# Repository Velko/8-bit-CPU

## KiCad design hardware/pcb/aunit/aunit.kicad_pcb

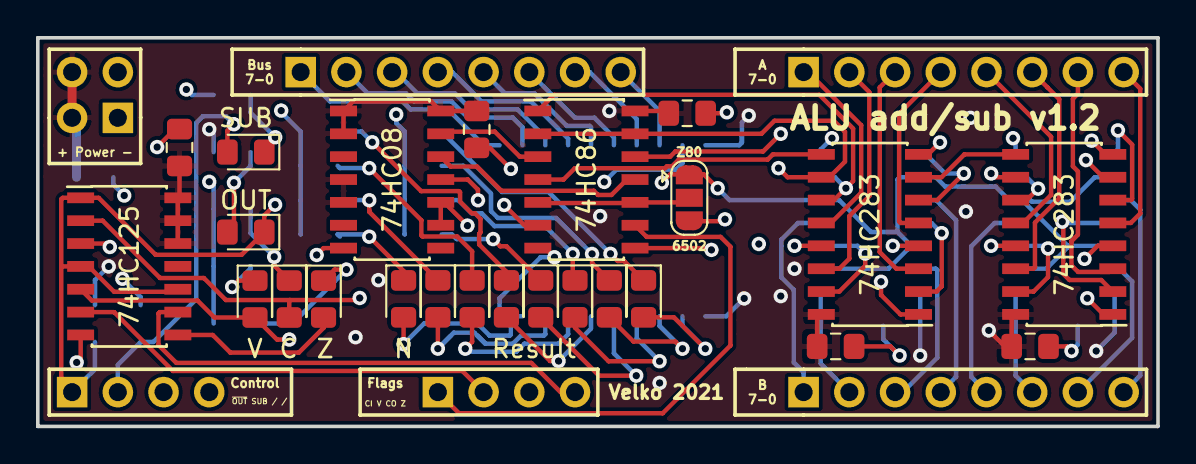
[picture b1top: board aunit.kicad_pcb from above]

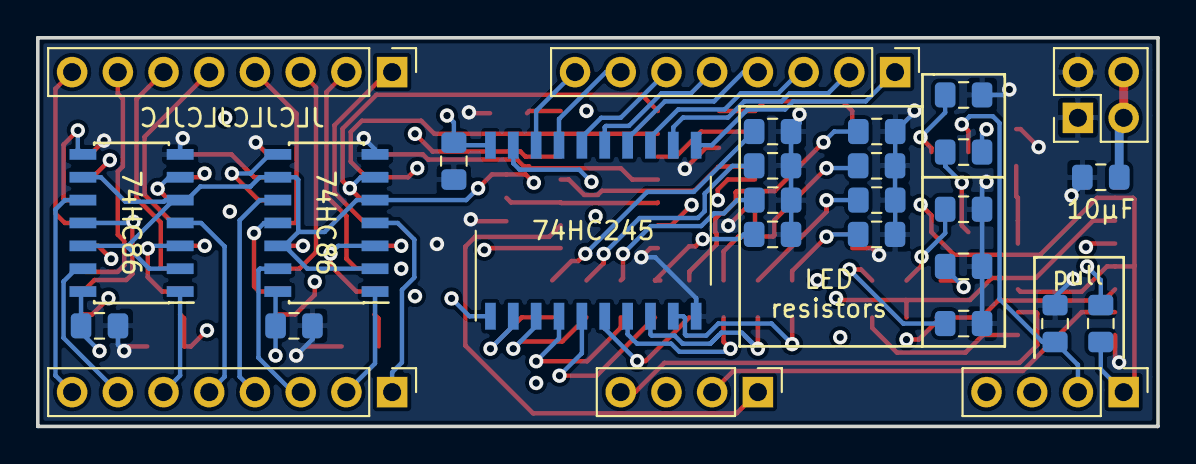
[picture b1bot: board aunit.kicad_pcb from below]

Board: 4 copper layers, 62.2 x 21.6 mm, 52 parts (28 on the bottom side), 70 nets.

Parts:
C1: 10μF; C_0805_2012Metric_Pad1.15x1.40mm_HandSolder
C2, C3, C4, C5, C6, C7, C8, C9: 100nF; C_0805_2012Metric_Pad1.15x1.40mm_HandSolder
D0: 0; LED_0805_2012Metric_Pad1.15x1.40mm_HandSolder
D1: 1; LED_0805_2012Metric_Pad1.15x1.40mm_HandSolder
D2: 2; LED_0805_2012Metric_Pad1.15x1.40mm_HandSolder
D3: Result; LED_0805_2012Metric_Pad1.15x1.40mm_HandSolder
D4: 4; LED_0805_2012Metric_Pad1.15x1.40mm_HandSolder
D5: 5; LED_0805_2012Metric_Pad1.15x1.40mm_HandSolder
D6: 6; LED_0805_2012Metric_Pad1.15x1.40mm_HandSolder
D7: N; LED_0805_2012Metric_Pad1.15x1.40mm_HandSolder
D8: OUT; LED_0805_2012Metric_Pad1.15x1.40mm_HandSolder
D9: V; LED_0805_2012Metric_Pad1.15x1.40mm_HandSolder
D10: C; LED_0805_2012Metric_Pad1.15x1.40mm_HandSolder
D11: SUB; LED_0805_2012Metric_Pad1.15x1.40mm_HandSolder
D12: Z; LED_0805_2012Metric_Pad1.15x1.40mm_HandSolder
J1: BUS; PinHeader_1x08_P2.54mm_Vertical
J2: Input A; PinHeader_1x08_P2.54mm_Vertical
J3: Input B; PinHeader_1x08_P2.54mm_Vertical
J4: Control; PinHeader_1x04_P2.54mm_Vertical
J5: Flags; PinHeader_1x04_P2.54mm_Vertical
J6: Power; PinHeader_2x02_P2.54mm_Vertical
JP1: SolderJumper_3_Open; SolderJumper-3_P1.3mm_Open_RoundedPad1.0x1.5mm
R0, R1, R2, R3, R4, R5, R6, R7, R8, R9, R10, R11, R14: 330; R_0805_2012Metric_Pad1.15x1.40mm_HandSolder
R12, R13: 10K; R_0805_2012Metric_Pad1.15x1.40mm_HandSolder
U1, U2: 74HC283; SOIC-16_3.9x9.9mm_P1.27mm
U3, U4, U5: 74HC86; SOIC-14_3.9x8.7mm_P1.27mm
U6: 74HC08; SOIC-14_3.9x8.7mm_P1.27mm
U7: 74HC245; SO-20_12.8x7.5mm_P1.27mm
U8: 74HC125; SOIC-14_3.9x8.7mm_P1.27mm

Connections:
/B0I: U1.6, U3.8
/B1I: U1.2, U3.11
/B2I: U1.15, U3.3
/B3I: U1.11, U3.6
/B4I: U2.6, U4.8
/B5I: U2.2, U4.11
/B6I: U2.15, U4.3
/CII: U1.7, U5.8
/CO: U2.9, U5.4
A0: J2.8, U1.5
A1: J2.7, U1.3
A2: J2.6, U1.14
A3: J2.5, U1.12
A4: J2.4, U2.5
A5: J2.3, U2.3
A6: J2.2, U2.14
A7: J2.1, U2.12, U5.12
ADD_SUB: D11.2, J4.2, JP1.1, R13.2, U3.2, U3.5, U3.9, U3.12, U4.2, U4.5, U4.9, U4.12
B0: J3.8, U3.10
B1: J3.7, U3.13
B2: J3.6, U3.1
B3: J3.5, U3.4
B4: J3.4, U4.10
B5: J3.3, U4.13
B6: J3.2, U4.1
B7: J3.1, U4.4
B7I: U2.11, U4.6, U5.1
BUS0: J1.8, U7.18
BUS1: J1.7, U7.17
BUS2: J1.6, U7.16
BUS3: J1.5, U7.15
BUS4: J1.4, U7.14
BUS5: J1.3, U7.13
BUS6: J1.2, U7.12
BUS7: J1.1, U7.11
CARRYD: D10.2, U5.6, U8.2
CIN: J5.1, U5.9
COUT: J5.3, U8.3
GND: C1.2, C2.2, C3.2, C4.2, C5.2, C6.2, C7.2, C8.2, C9.2, J6.1, J6.2, JP1.3, R0.1, R1.1, R2.1, R3.1, R4.1, R5.1, R6.1, R7.1, R9.1, R10.1, R11.1, R13.1, R14.1, U1.8, U2.8, U3.7, U4.7, U5.7, U6.7, U6.9, U6.10, U7.10, U8.7
unnamed: D0.1, R0.2
unnamed: D1.1, R1.2
unnamed: D2.1, R2.2
unnamed: D3.1, R3.2
unnamed: D4.1, R4.2
unnamed: D5.1, R5.2
unnamed: D6.1, R6.2
unnamed: D7.1, R7.2
unnamed: D8.2, R8.2
unnamed: D9.1, R9.2
unnamed: D10.1, R10.2
unnamed: D11.1, R11.2
unnamed: D12.1, R14.2
unnamed: D12.2, U8.8
unnamed: JP1.2, U5.5, U5.10
unnamed: U1.9, U2.7
unnamed: U5.3, U6.13
unnamed: U5.11, U6.12
OOUT: J5.2, U8.6
OVFD: D9.2, U6.11, U8.5
SUM0: D0.2, U1.4, U7.2
SUM1: D1.2, U1.1, U7.3
SUM2: D2.2, U1.13, U7.4
SUM3: D3.2, U1.10, U7.5
SUM4: D4.2, U2.4, U7.6
SUM5: D5.2, U2.1, U7.7
SUM6: D6.2, U2.13, U7.8
SUM7: D7.2, U2.10, U5.2, U5.13, U7.9
VCC: C1.1, C2.1, C3.1, C4.1, C5.1, C6.1, C7.1, C8.1, C9.1, J6.3, J6.4, R8.1, R12.2, U1.16, U2.16, U3.14, U4.14, U5.14, U6.1, U6.2, U6.4, U6.5, U6.14, U7.1, U7.20, U8.12, U8.13, U8.14
ZIN: J5.4, U8.9
~OUT~: D8.1, J4.1, R12.1, U7.19, U8.1, U8.4, U8.10

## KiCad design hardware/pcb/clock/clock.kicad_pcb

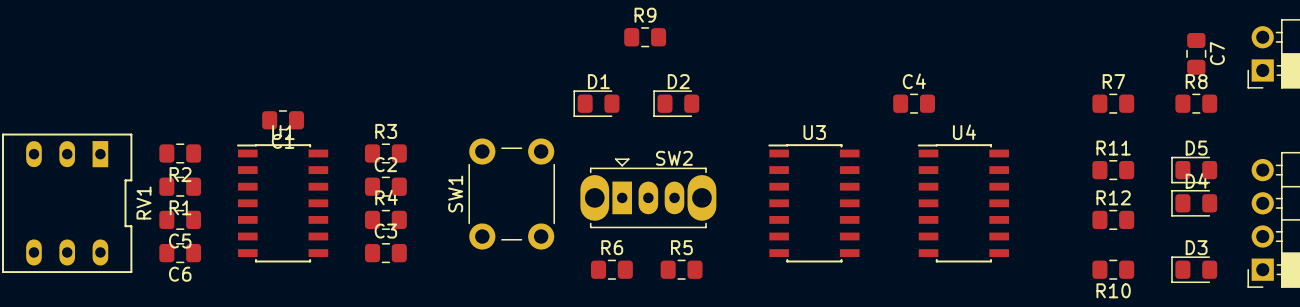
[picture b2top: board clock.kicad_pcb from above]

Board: 2 copper layers, 32 parts (0 on the bottom side), 26 nets, no tracks yet.

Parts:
C1, C3, C4, C7: 100nF; C_0805_2012Metric_Pad1.15x1.40mm_HandSolder
C2, C5: 10nF; C_0805_2012Metric_Pad1.15x1.40mm_HandSolder
C6: 1μF; C_0805_2012Metric_Pad1.15x1.40mm_HandSolder
D1, D2, D3, D4, D5: LED; LED_0805_2012Metric_Pad1.15x1.40mm_HandSolder
J1: 01x02_F; PinSocket_1x02_P2.54mm_Horizontal
J2: 01x04_F; PinSocket_1x04_P2.54mm_Horizontal
R1, R2, R3: 1K; R_0805_2012Metric_Pad1.15x1.40mm_HandSolder
R4: 1M; R_0805_2012Metric_Pad1.15x1.40mm_HandSolder
R5, R6, R7, R8: 10K; R_0805_2012Metric_Pad1.15x1.40mm_HandSolder
R9, R10, R11, R12: 330; R_0805_2012Metric_Pad1.15x1.40mm_HandSolder
RV1: 1M; POT_DIP_Dual_Vert
SW1: SW_Push; SW_PUSH_6mm
SW2: SW_SPDT; SW_Slide_1P2T_CK_OS102011MS2Q
U1: TLC556; SOIC-14_3.9x8.7mm_P1.27mm
U3: 74HC02; SOIC-14_3.9x8.7mm_P1.27mm
U4: 74HC00; SOIC-14_3.9x8.7mm_P1.27mm

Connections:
CLK: D3.1, J2.1, U3.5, U3.6, U4.8
GND: C1.2, C2.2, C3.2, C4.2, C5.2, C6.2, C7.2, J1.1, R5.2, R6.2, R8.2, R9.2, R10.2, R11.2, SW1.1, U1.7, U3.2, U3.3, U3.7, U4.7
HLT: D4.1, J2.3, R8.1, U4.13
unnamed: C2.1, U1.11
unnamed: C3.1, R4.2, U1.12, U1.13
unnamed: C5.1, U1.3
unnamed: C6.1, RV1.1, U1.2, U1.6
unnamed: D1.1, U3.9, U3.13, U4.2
unnamed: D1.2, D2.2, R9.1
unnamed: D2.1, U3.10, U3.11, U4.5
unnamed: D3.2, R10.1
unnamed: D4.2, R11.1
unnamed: D5.1, R12.2
unnamed: R1.2, R2.2, U1.1
unnamed: R2.1, RV1.2
unnamed: R3.2, SW1.2, U1.8
unnamed: R5.1, SW2.3, U3.12
unnamed: R6.1, SW2.1, U3.8
unnamed: U1.5, U4.1
unnamed: U1.9, U4.4
unnamed: U1.4, U1.10, U4.11
unnamed: U4.3, U4.9
unnamed: U4.6, U4.10
VCC: C1.1, C4.1, C7.1, J1.2, R1.1, R3.1, R4.1, R7.1, R12.1, SW2.2, U1.14, U3.14, U4.14
~CLK~: J2.2, U3.4
~WAKE~: D5.2, J2.4, R7.2, U4.12

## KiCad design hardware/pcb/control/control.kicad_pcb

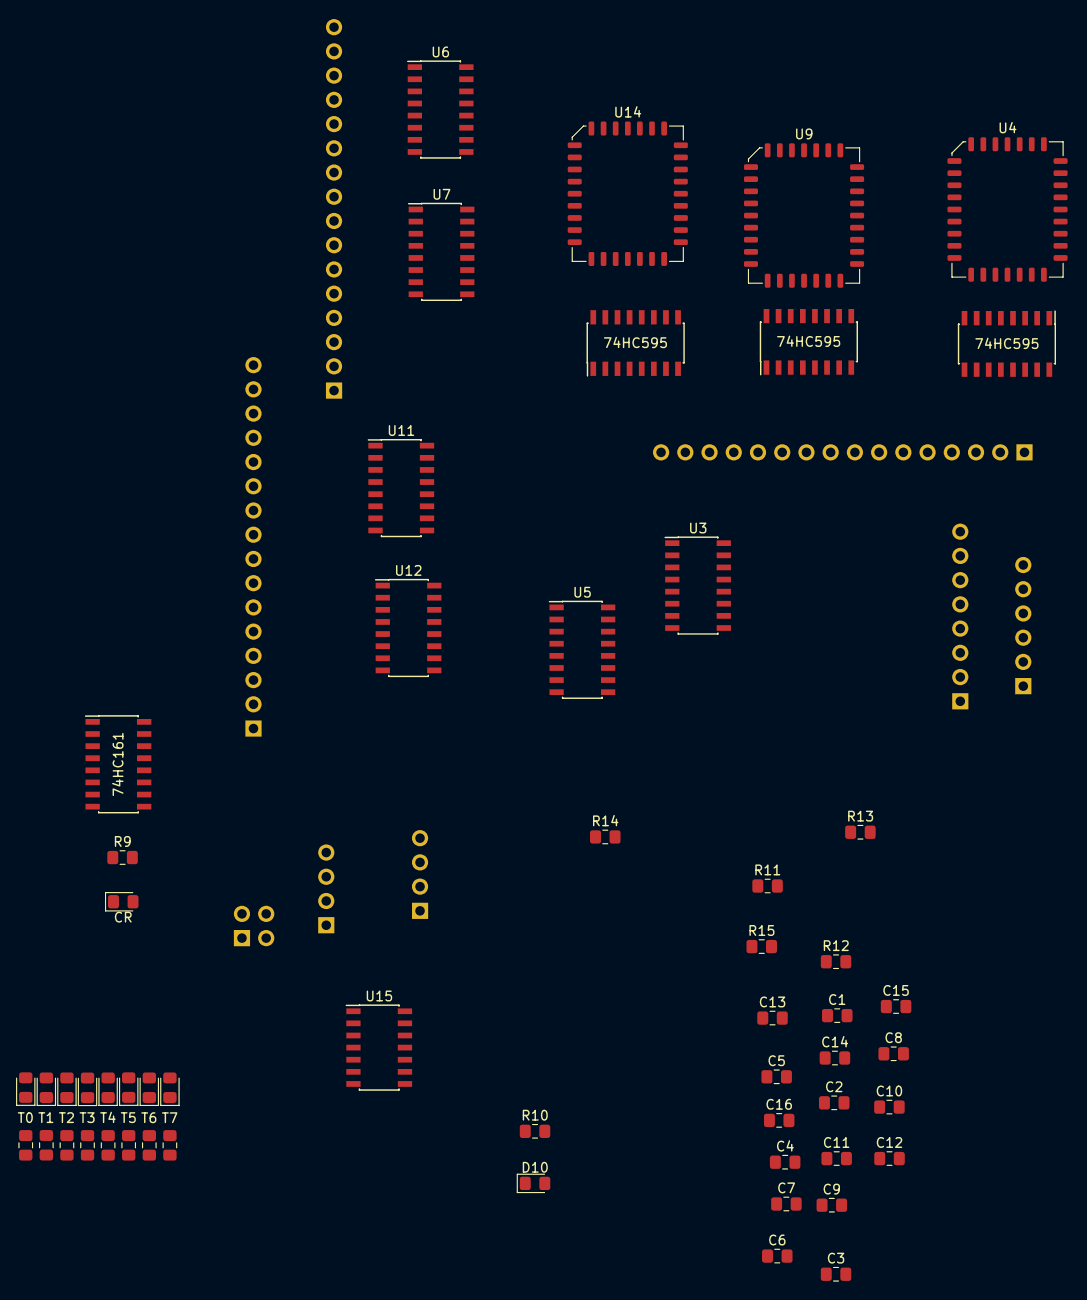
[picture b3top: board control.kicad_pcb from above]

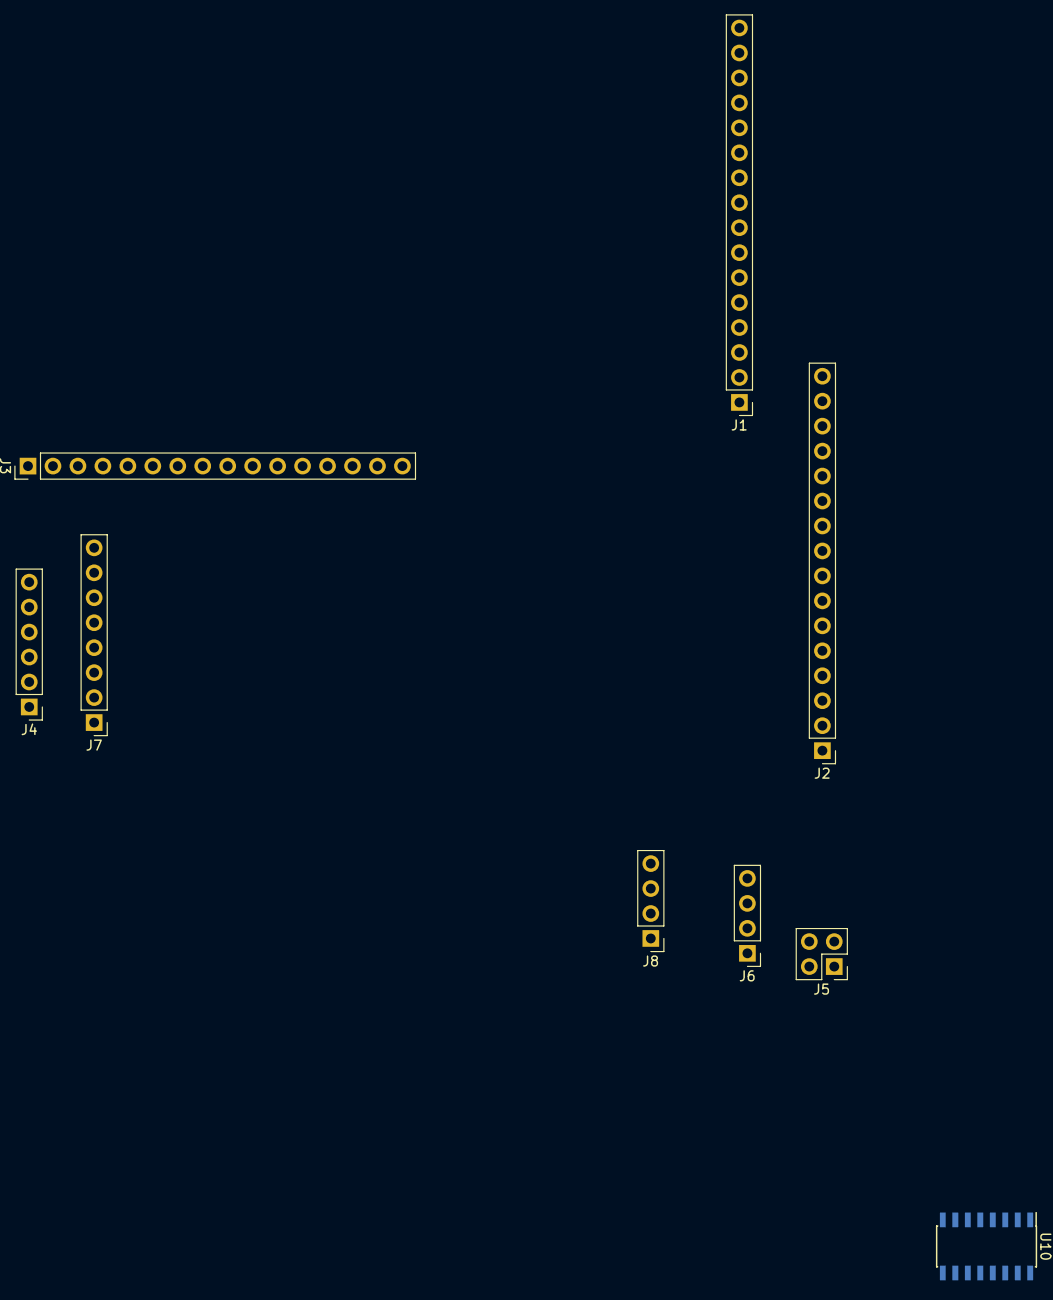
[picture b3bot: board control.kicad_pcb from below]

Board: 2 copper layers, 64 parts (9 on the bottom side), 103 nets, no tracks yet.

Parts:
C1, C2, C3, C4, C5, C6, C7, C8, C9, C10, C11, C12, C13, C14, C15: 100nF; C_0805_2012Metric_Pad1.15x1.40mm_HandSolder
C16: 10uF; C_0805_2012Metric_Pad1.15x1.40mm_HandSolder
D1: T0; LED_0805_2012Metric_Pad1.15x1.40mm_HandSolder
D2: T1; LED_0805_2012Metric_Pad1.15x1.40mm_HandSolder
D3: T2; LED_0805_2012Metric_Pad1.15x1.40mm_HandSolder
D4: T3; LED_0805_2012Metric_Pad1.15x1.40mm_HandSolder
D5: T4; LED_0805_2012Metric_Pad1.15x1.40mm_HandSolder
D6: T5; LED_0805_2012Metric_Pad1.15x1.40mm_HandSolder
D7: T6; LED_0805_2012Metric_Pad1.15x1.40mm_HandSolder
D8: T7; LED_0805_2012Metric_Pad1.15x1.40mm_HandSolder
D9: CR; LED_0805_2012Metric_Pad1.15x1.40mm_HandSolder
D10: SPI; LED_0805_2012Metric_Pad1.15x1.40mm_HandSolder
J1: OUT; PinHeader_1x16_P2.54mm_Vertical
J2: LOAD; PinHeader_1x16_P2.54mm_Vertical
J3: GPCTRL; PinHeader_1x16_P2.54mm_Vertical
J4: SPI; PinHeader_1x06_P2.54mm_Vertical
J5: POWER; PinHeader_2x02_P2.54mm_Vertical
J6: FLAGS; PinHeader_1x04_P2.54mm_Vertical
J7: Instruction; PinHeader_1x08_P2.54mm_Vertical
J8: SYNC; PinHeader_1x04_P2.54mm_Vertical
R1, R2, R3, R4, R5, R6, R7, R8, R9, R10: 330; R_0805_2012Metric_Pad1.15x1.40mm_HandSolder
R11: 100K; R_0805_2012Metric_Pad1.15x1.40mm_HandSolder
R12, R13, R14, R15: 10K; R_0805_2012Metric_Pad1.15x1.40mm_HandSolder
U1: 74HC161; SOIC-16_3.9x9.9mm_P1.27mm
U2, U8, U13: 74HC595; SOIC-16_3.9x9.9mm_P1.27mm
U3, U5: 74HC597; SOIC-16_3.9x9.9mm_P1.27mm
U4, U9, U14: SST39SF010; PLCC-32_11.4x14.0mm_P1.27mm
U6, U7, U10, U11, U12: 74HC138; SOIC-16_3.9x9.9mm_P1.27mm
U15: 74HC04; SOIC-14_3.9x8.7mm_P1.27mm

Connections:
ALOAD0: U8.15, U9.13, U11.1, U12.1
ALOAD1: U8.1, U9.14, U11.2, U12.2
ALOAD2: U8.2, U9.15, U11.3, U12.3
ALOAD3: U8.3, U9.17, U11.4, U12.6
AOUT0: U2.15, U4.13, U6.1, U7.1
AOUT1: U2.1, U4.14, U6.2, U7.2
AOUT2: U2.2, U4.15, U6.3, U7.3
AOUT3: U2.3, U4.17, U6.4, U7.6
CLK_INV: J8.2, U1.2
FLGC: J6.3, U4.5, U5.5, U9.5, U14.5
FLGN: J6.1, U4.7, U5.3, U9.7, U14.7
FLGV: J6.4, U4.27, U5.6, U9.27, U14.27
FLGZ: J6.2, U4.6, U5.4, U9.6, U14.6
GND: C1.2, C2.2, C3.2, C4.2, C5.2, C6.2, C7.2, C8.2, C9.2, C10.2, C11.2, C12.2, C13.2, C14.2, C15.2, C16.2, J5.1, J5.2, R12.1, R13.1, R14.1, R15.1, U1.3, U1.4, U1.5, U1.6, U1.8, U2.8, U3.8, U4.11, U4.12, U4.16, U4.22, U5.7, U5.8, U5.14, U6.5, U6.8, U7.4, U7.5, U7.8, U8.8, U9.11, U9.16, U9.22, U10.4, U10.5, U10.8, U11.5, U11.8, U12.4, U12.5, U12.8, U13.8, U14.12, U14.16, U14.22
GPCTRL0: J3.16, U2.4, U4.18
GPCTRL1: J3.15, U2.5, U4.19
GPCTRL2: J3.14, U2.6, U4.20
GPCTRL3: J3.13, U8.4, U9.18
GPCTRL4: J3.12, U8.5, U9.19
GPCTRL5: J3.11, U8.6, U9.20
GPCTRL6: J3.10, U8.7, U9.21
GPCTRL7: J3.9, U13.15, U14.13
GPCTRL8: J3.8, U13.1, U14.14
GPCTRL9: J3.7, U13.2, U14.15
GPCTRL10: J3.6, U13.3, U14.17
GPCTRL11: J3.5, U13.4, U14.18
GPCTRL12: J3.4, U13.5, U14.19
GPCTRL13: J3.3, U13.6, U14.20
GPCTRL14: J3.2, U13.7, U14.21
INSTR0: J7.1, U3.15, U4.26, U9.26, U14.26
INSTR1: J7.2, U3.1, U4.23, U9.23, U14.23
INSTR2: J7.3, U3.2, U4.25, U9.25, U14.25
INSTR3: J7.4, U3.3, U4.4, U9.4, U14.4
INSTR4: J7.5, U3.4, U4.28, U9.28, U14.28
INSTR5: J7.6, U3.5, U4.29, U9.29, U14.29
INSTR6: J7.7, U3.6, U4.3, U9.3, U14.3
INSTR7: J7.8, U3.7, U4.2, U9.2, U14.2
LOADCTRL0: J2.16, U11.15
LOADCTRL1: J2.15, U11.14
LOADCTRL2: J2.14, U11.13
LOADCTRL3: J2.13, U11.12
LOADCTRL4: J2.12, U11.11
LOADCTRL5: J2.11, U11.10
LOADCTRL6: J2.10, U11.9
LOADCTRL7: J2.9, U11.7
LOADCTRL8: J2.8, U12.15
LOADCTRL9: J2.7, U12.14
LOADCTRL10: J2.6, U12.13
LOADCTRL11: J2.5, U12.12
LOADCTRL12: J2.4, U12.11
LOADCTRL13: J2.3, U12.10
LOADCTRL14: J2.2, U12.9
LOADCTRL15: J2.1, U12.7
MISO8: U3.14, U5.9
MOSI8: U2.9, U8.14
MOSI16: U8.9, U13.14
unnamed: D1.1, R1.1
unnamed: D2.1, R2.1
unnamed: D3.1, R3.1
unnamed: D4.1, R4.1
unnamed: D5.1, R5.1
unnamed: D6.1, R6.1
unnamed: D7.1, R7.1
unnamed: D8.1, R8.1
unnamed: D9.1, R9.1
unnamed: D10.1, R10.1
unnamed: R1.2, U10.15
unnamed: R2.2, U10.14
unnamed: R3.2, U10.13
unnamed: R4.2, U10.12
unnamed: R5.2, U10.11
unnamed: R6.2, U10.10
unnamed: R7.2, U10.9
unnamed: R8.2, U10.7
OUTCTRL0: J1.16, U6.15
OUTCTRL1: J1.15, U6.14
OUTCTRL2: J1.14, U6.13
OUTCTRL3: J1.13, U6.12
OUTCTRL4: J1.12, U6.11
OUTCTRL5: J1.11, U6.10
OUTCTRL6: J1.10, U6.9
OUTCTRL7: J1.9, U6.7
OUTCTRL8: J1.8, U7.15
OUTCTRL9: J1.7, U7.14
OUTCTRL10: J1.6, U7.13
OUTCTRL11: J1.5, U7.12
OUTCTRL12: J1.4, U7.11
OUTCTRL13: J1.3, U7.10
OUTCTRL14: J1.2, U7.9
OUTCTRL15: J1.1, U7.7
ROM_OE: J4.5, R15.2, U4.24, U9.24, U14.24, U15.3
SPI_LATCH: J4.1, R12.2, U2.12, U3.12, U5.12, U8.12, U13.12, U15.1
SPI_MISO: J4.3, U3.9
SPI_MOSI: J4.2, R13.2, U2.14
SPI_OE: R10.2, U2.13, U8.13, U13.13, U15.4
SPI_SCK: J4.4, R14.2, U2.11, U3.11, U5.11, U8.11, U13.11
SRESET: R9.2, U1.9, U2.7, U4.21
STEP0: U1.14, U4.10, U5.15, U9.10, U10.1, U14.10
STEP1: U1.13, U4.9, U5.1, U9.9, U10.2, U14.9
STEP2: U1.12, U4.8, U5.2, U9.8, U10.3, U14.8
VCC: C1.1, C2.1, C3.1, C4.1, C5.1, C6.1, C7.1, C8.1, C9.1, C10.1, C11.1, C12.1, C13.1, C14.1, C15.1, C16.1, D1.2, D2.2, D3.2, D4.2, D5.2, D6.2, D7.2, D8.2, D9.2, D10.2, J5.3, J5.4, R11.1, U1.7, U1.10, U1.16, U2.10, U2.16, U3.10, U3.16, U4.31, U4.32, U5.10, U5.16, U6.6, U6.16, U7.16, U8.10, U8.16, U9.12, U9.31, U9.32, U10.6, U10.16, U11.6, U11.16, U12.16, U13.10, U13.16, U14.11, U14.31, U14.32
~RESET~: J8.4, R11.2, U1.1
~SPI_PL~: U3.13, U5.13, U15.2

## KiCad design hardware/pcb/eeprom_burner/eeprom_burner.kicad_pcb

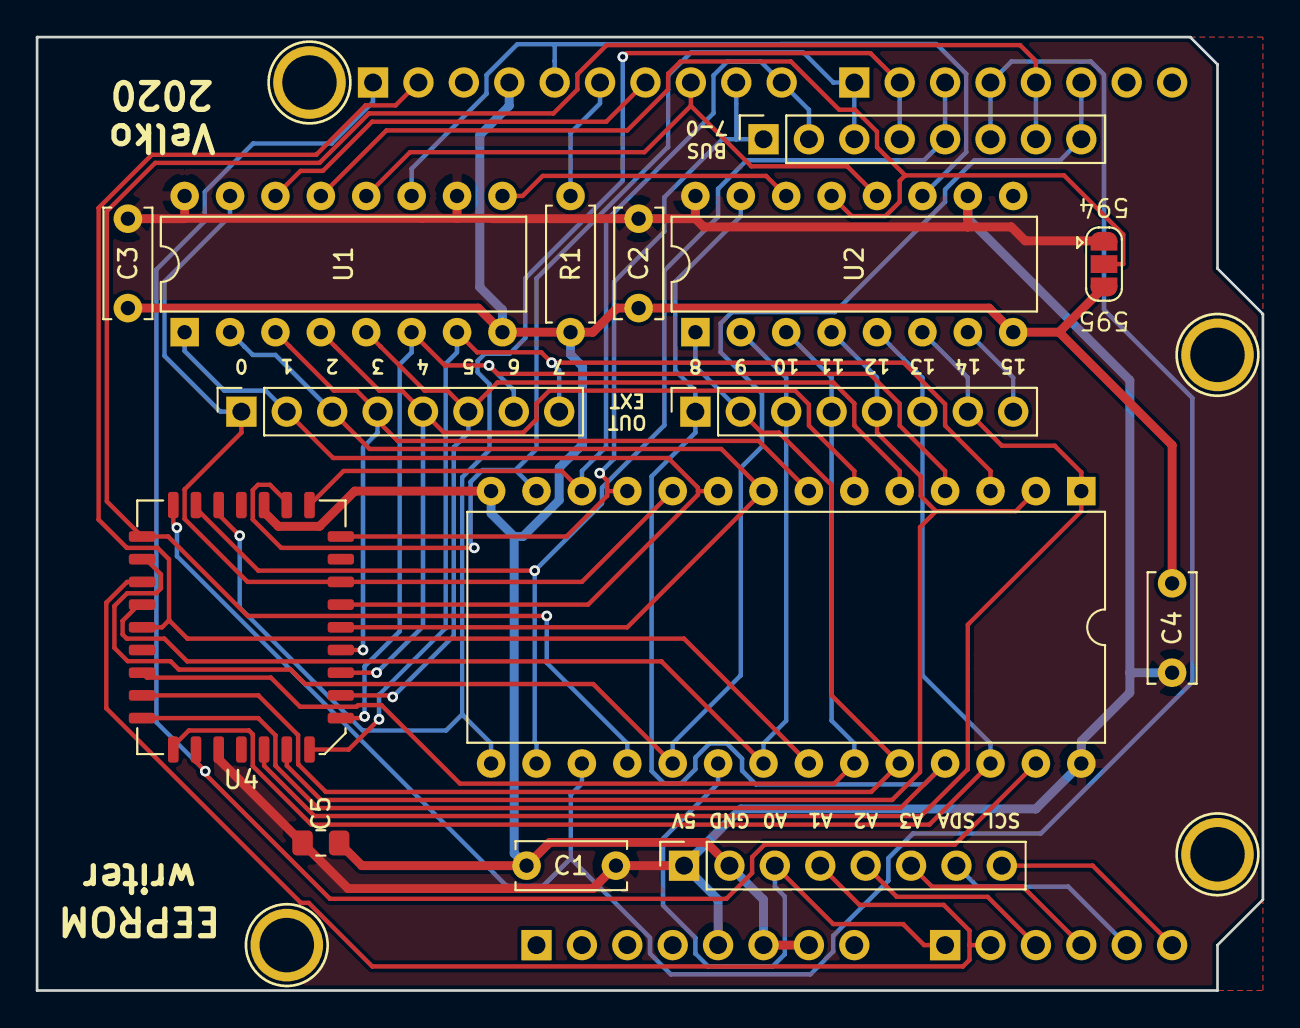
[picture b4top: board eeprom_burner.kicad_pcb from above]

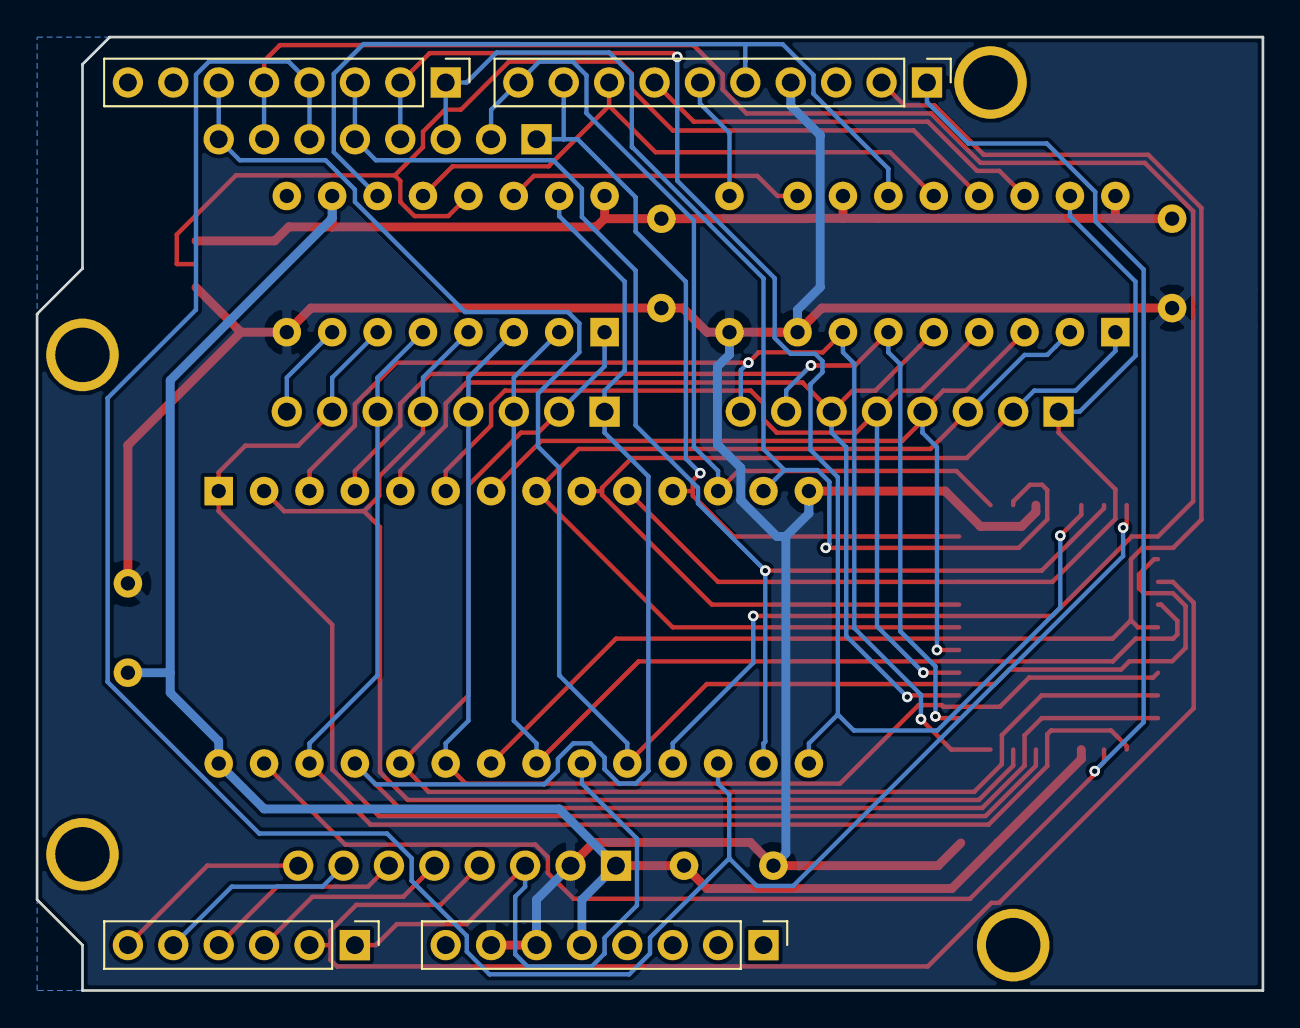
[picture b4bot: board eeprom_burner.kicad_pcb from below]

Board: 2 copper layers, 68.6 x 53.3 mm, 23 parts (4 on the bottom side), 40 nets.

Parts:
C1, C2, C3, C4: 100nF; C_Disc_D6.0mm_W2.5mm_P5.00mm
C5: 100nF; C_0805_2012Metric_Pad1.15x1.40mm_HandSolder
J1, J2, J3: Conn_01x08; PinSocket_1x08_P2.54mm_Vertical
J4: Conn_01x06; PinSocket_1x08_P2.54mm_Vertical
JP1: SolderJumper_3_Open; SolderJumper-3_P1.3mm_Open_RoundedPad1.0x1.5mm
P1: Power; PinHeader_1x08_P2.54mm_Vertical
P2: Analog; PinHeader_1x06_P2.54mm_Vertical
P3: Digital; PinHeader_1x10_P2.54mm_Vertical
P4: Digital; PinHeader_1x08_P2.54mm_Vertical
P5, P6, P7, P8: CONN_01X01; Arduino_1pin
R1: 10K; R_Axial_DIN0207_L6.3mm_D2.5mm_P7.62mm_Horizontal
U1, U2: 74HC595; DIP-16_W7.62mm
U3: 28C256; DIP-28_W15.24mm
U4: 28C256J; PLCC-32_11.4x14.0mm_P1.27mm

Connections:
+5V: C1.1, C2.1, C3.1, C4.1, C5.1, J4.1, JP1.1, P1.5, U1.10, U1.16, U2.10, U2.16, U3.28, U4.32
A0: J1.1, U1.15, U3.10, U4.11
A1: J1.2, U1.1, U3.9, U4.10
A2: J1.3, U1.2, U3.8, U4.9
A3: J1.4, U1.3, U3.7, U4.8
A4: J1.5, U1.4, U3.6, U4.7
A5: J1.6, U1.5, U3.5, U4.6
A6: J1.7, U1.6, U3.4, U4.5
A7: J1.8, U1.7, U3.3, U4.4
A8: J2.1, U2.15, U3.25, U4.29
A9: J2.2, U2.1, U3.24, U4.28
A10: J2.3, U2.2, U3.21, U4.24
A11: J2.4, U2.3, U3.23, U4.27
A12: J2.5, U2.4, U3.2, U4.3
A13: J2.6, U2.5, U3.26, U4.30
A14: J2.7, U2.6, U3.1, U4.2
A15: J2.8, U2.7
D0: J3.1, P3.9, U3.11, U4.13
D1: J3.2, P3.10, U3.12, U4.14
D2: J3.3, P4.1, U3.13, U4.15
D3: J3.4, P4.2, U3.15, U4.18
D4: J3.5, P4.3, U3.16, U4.19
D5: J3.6, P4.4, U3.17, U4.20
D6: J3.7, P4.5, U3.18, U4.21
D7: J3.8, P4.6, U3.19, U4.22
E0: J4.3, P2.1, U3.20
E1: J4.4, P2.2, U4.23
E2: J4.5, P2.3
E3: J4.6, P2.4
E4: J4.7, P2.5
E5: J4.8, P2.6
GND: C1.2, C2.2, C3.2, C4.2, C5.2, J4.2, JP1.3, P1.6, P1.7, P3.4, R1.2, U1.8, U2.8, U3.14, U4.16
LATCH: P3.8, U1.12, U2.12
MISO: P3.6, R1.1
MOSI: P3.7, U1.14
unnamed: JP1.2, U1.13, U2.13
unnamed: U1.9, U2.14
SCK: P3.5, U1.11, U2.11
~OE~: P3.2, U3.22, U4.25
~WE~: P3.1, U3.27, U4.31

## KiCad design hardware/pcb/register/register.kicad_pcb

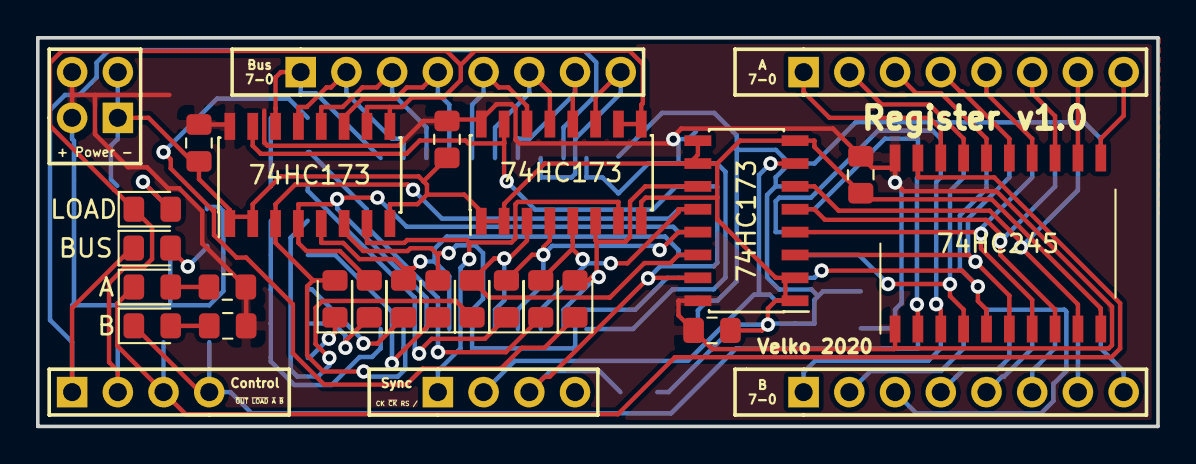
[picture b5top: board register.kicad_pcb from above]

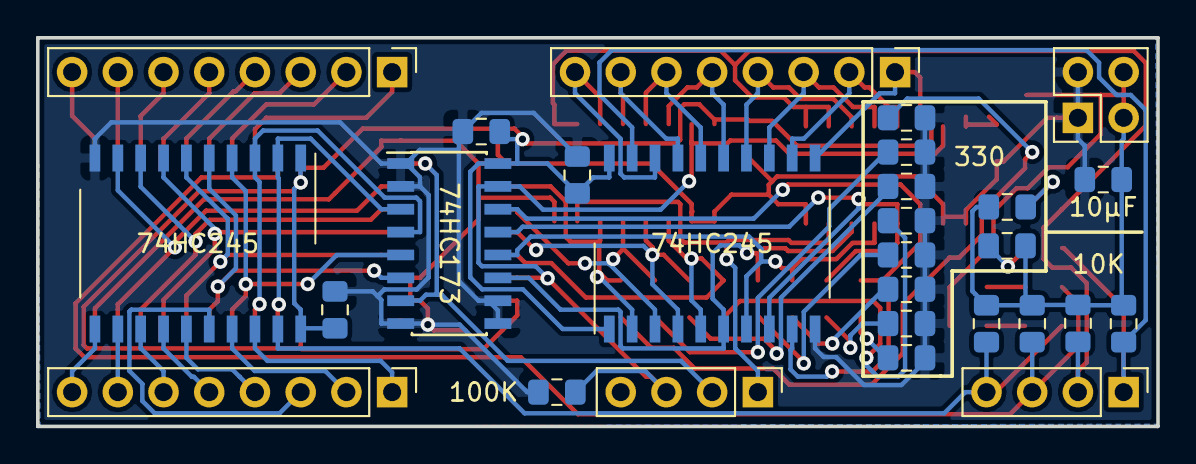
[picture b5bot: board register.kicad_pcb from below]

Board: 2 copper layers, 62.2 x 21.6 mm, 50 parts (28 on the bottom side), 61 nets.

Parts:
C1, C3, C4, C5, C6, C7, C8: 100nF; C_0805_2012Metric_Pad1.15x1.40mm_HandSolder
C2: 10µF; C_0805_2012Metric_Pad1.15x1.40mm_HandSolder
D1, D2, D3, D4, D5, D6, D7, D8: LED; LED_0805_2012Metric_Pad1.15x1.40mm_HandSolder
D9: LOAD; LED_0805_2012Metric_Pad1.15x1.40mm_HandSolder
D10: BUS; LED_0805_2012Metric_Pad1.15x1.40mm_HandSolder
D11: A; LED_0805_2012Metric_Pad1.15x1.40mm_HandSolder
D12: B; LED_0805_2012Metric_Pad1.15x1.40mm_HandSolder
J1, J5, J6: Conn_01x08_Male; PinHeader_1x08_P2.54mm_Vertical
J2, J3: Conn_01x04_Male; PinHeader_1x04_P2.54mm_Vertical
J4: Conn_01x04_Male; PinHeader_2x02_P2.54mm_Vertical
R1, R2, R3, R4: 10K; R_0805_2012Metric_Pad1.15x1.40mm_HandSolder
R5, R6, R7, R8, R9, R10, R11, R12, R14, R15, R16, R17: 330; R_0805_2012Metric_Pad1.15x1.40mm_HandSolder
R13: 100K; R_0805_2012Metric_Pad1.15x1.40mm_HandSolder
U1, U6, U7: 74HC245; SO-20_12.8x7.5mm_P1.27mm
U2, U3, U4, U5: 74HC173; SOIC-16_3.9x9.9mm_P1.27mm

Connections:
A0: J5.8, U6.11
A1: J5.7, U6.12
A2: J5.6, U6.13
A3: J5.5, U6.14
A4: J5.4, U6.15
A5: J5.3, U6.16
A6: J5.2, U6.17
A7: J5.1, U6.18
B0: J6.8, U7.11
B1: J6.7, U7.12
B2: J6.6, U7.13
B3: J6.5, U7.14
B4: J6.4, U7.15
B5: J6.3, U7.16
B6: J6.2, U7.17
B7: J6.1, U7.18
BUS0: J1.8, U1.18, U2.11
BUS1: J1.7, U1.17, U2.12
BUS2: J1.6, U1.16, U2.13
BUS3: J1.5, U1.15, U2.14
BUS4: J1.4, U1.14, U4.11
BUS5: J1.3, U1.13, U4.12
BUS6: J1.2, U1.12, U4.13
BUS7: J1.1, U1.11, U4.14
CLK: J3.1, U2.7, U4.7
GND: C1.2, C2.2, C3.2, C4.2, C5.2, C6.2, C7.2, C8.2, J4.1, J4.2, R5.1, R6.1, R7.1, R8.1, R9.1, R10.1, R11.1, R12.1, R13.1, U1.10, U2.1, U2.2, U2.8, U3.1, U3.2, U3.8, U3.9, U3.10, U4.1, U4.2, U4.8, U5.1, U5.2, U5.8, U5.9, U5.10, U6.10, U7.10
M0: D1.2, U1.2, U2.6, U3.11
M1: D2.2, U1.3, U2.5, U3.12
M2: D3.2, U1.4, U2.4, U3.13
M3: D4.2, U1.5, U2.3, U3.14
M4: D5.2, U1.6, U4.6, U5.11
M5: D6.2, U1.7, U4.5, U5.12
M6: D7.2, U1.8, U4.4, U5.13
M7: D8.2, U1.9, U4.3, U5.14
unnamed: D1.1, R5.2
unnamed: D2.1, R6.2
unnamed: D3.1, R7.2
unnamed: D4.1, R8.2
unnamed: D5.1, R9.2
unnamed: D6.1, R10.2
unnamed: D7.1, R11.2
unnamed: D8.1, R12.2
unnamed: D9.2, R17.2
unnamed: D10.2, R14.2
unnamed: D11.2, R15.2
unnamed: D12.2, R16.2
RESET: J3.3, R13.2, U2.15, U3.15, U4.15, U5.15
TAP0: U3.6, U6.9, U7.9
TAP1: U3.5, U6.8, U7.8
TAP2: U3.4, U6.7, U7.7
TAP3: U3.3, U6.6, U7.6
TAP4: U5.6, U6.5, U7.5
TAP5: U5.5, U6.4, U7.4
TAP6: U5.4, U6.3, U7.3
TAP7: U5.3, U6.2, U7.2
VCC: C1.1, C2.1, C3.1, C4.1, C5.1, C6.1, C7.1, C8.1, J4.3, J4.4, R1.1, R2.1, R3.2, R4.1, R14.1, R15.1, R16.1, R17.1, U1.1, U1.20, U2.16, U3.16, U4.16, U5.16, U6.1, U6.20, U7.1, U7.20
~A_OUT~: D11.1, J2.3, R2.2, U6.19
~BUS_OUT~: D10.1, J2.1, R1.2, U1.19
~B_OUT~: D12.1, J2.4, R4.2, U7.19
~CLK~: J3.2, U3.7, U5.7
~LOAD~: D9.1, J2.2, R3.1, U2.9, U2.10, U4.9, U4.10
